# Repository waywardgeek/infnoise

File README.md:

### Infinite Noise TRNG (True Random Number Generator)

For instructions for compiling the and using Infinite Noise TRNG driver, go to the software
sub-directory, and read the [README](software/README.md) file there.  Both Linux and Windows
are supported.

The Infinite Noise TRNG is a USB key hardware true random number generator.  It uses what
I call a "Modular Entropy Multiplier" architecture (previously Infinite Noise Multiplier or
FireBug).  Besides being simple, low-cost, and fast, it is much easier to get right than
other TRNGs.  It naturally defends against influence from outside signals, such as radio
interference and power supply noise, making it simple to build securely, without requiring
an expert in analog design.  Modular entropy multipliers produce a provable and easily
measured level of entropy based on thermal noise, approximately equal to log2(K) per
output bit, where K is a gain between 1 and 2 set by two resistors around an op-amp.  A
"health monitor" can track this and verify that the output entropy is within the expected
range, which for the Infinite Noise TRNG described below is within 2% of log2(1.82).

Modular entropy multipliers are suitable for both board level implementation and ASIC
implementation.  Speed is limited by the speed of a gain stage and a comparator, and can
run in excess of 100 Mbit/second per second with high performance components.  Cheap
solutions with CMOS quad op-amps can run at 8Mbit/second.

Adjacent bits from a modular entropy multiplier are correlated, so whitening is required
before use in cryptography.  This should be done by continually reseeding a
cryptographically secure hash function such as SHA-512, Blake2b, Keccak-1600 (SHA3), or a
stream cipher such as ChaCha.  This implementation uses Keccak-1600 with cryptographically
secure reseeding of more than 400 bits of entropy at a time, overcoming a trickle in/out
problem present in the GNU/Linux /dev/random system.  Users who need many megabytes per second
of data for use in cryptography can set the outputMultiplier as high as they like, which
causes Keccak to generate outputMultiplier\*256 bits per reseeding by the Infinite Noise
TRNG.

The modular entropy multiplier architecture was invented by Peter Allan in 1999, which he
called [Firebug](http://apa.hopto.org/firebug).  I reinvented it in 2013.  As usual, most
of my good ideas are rediscoveries of existing ideas :-)  Peter has his own
version called [the Redoubler](https://github.com/alwynallan/redoubler), which
is awesome.  It really is the _right_ way to generate random bits, whether on a
board with standard parts, or on an custom chip.

### Crowd Supply campaign

With the aid of crowdfunding, the Infinite Noise will soon be produced (again)! The campaign is driven by Manuel Domke, founder of a fresh electronics manufacturing company called 13-37.org electronics. 

[Check the Crowd Supply project page for latest updates](https://www.crowdsupply.com/13-37/infinite-noise-trng)

### The Eagle open-source boards work!

Here is the first completed Infinite Noise USB key.  I offered this model on
Tindie to help get the modular entropy multiplier concept out there initially.

Here are the first three boards from OSH Park.  They work _exactly_ as predicted.  They all
generate 300,000 bits per second, resulting in a measured 259,000 bits of entropy per second, which is within 0.5% of the predicted value of log2(1.82).

All three boards should produce log2(1.82) = 0.864 bits of entropy per bit by design.  The first one is estimated
to produce 0.867, while the second one produces 0.868, and the third is 0.867.

Here is the latest schematic:

![Schematic of Infinite Noise Multiplier](images/infnoise.png?raw=true "Infinite
Noise Multiplier")

Here is the latest board layout (thanks, EagleWorks!):

![Board layout of Infinite Noise Multiplier](images/infnoise_brd.png?raw=true "Infinite
Noise Multiplier")

The breadboard worked, too.  Estimated entropy per bit is 0.81 for the bread-board.  By design, it should
be 0.80, so it is very close to the prediction.  The breadboard proved out much of the theory of operation, as well os providing raw data for entropy testing.

![Breadboard of Infinite Noise Multiplier](images/infnoise_breadboard.jpg?raw=true "Infinite
Noise Multiplier")

Here is the voltage on one of the hold cap:

To build one of these for yourself, you can [order three boards from OSH Park for only
$3.25](https://oshpark.com/profiles/WaywardGeek), and then buy parts from [Digikey and
Mouser as described in the
BOM](https://github.com/waywardgeek/infnoise/blob/master/eagle/BOM.xlsx?raw=true).  I
designed this board to be cheap, not easy to assemble by hand.  I use 2 QFN parts and
three with 0.5mm lead pitch.  If you want to [build these yourself the way I
do](https://www.sparkfun.com/tutorials/59), consider uploading the [infnoise.brd
file](https://raw.githubusercontent.com/waywardgeek/infnoise/master/eagle/infnoise.brd) to
[OSH Stencils](https://www.oshstencils.com/) and ordering a solder paste stencil for $7.
I get the [solder paste from SparkFun](https://www.sparkfun.com/products/12878).  Kudos to
OSH Park, OSH Stencil, SmallBatchAssembly, and DigiSpark!  They're making this whole party
possible!

The total for all the parts, including boards from OSH Park, come to $5.69 each, in 1,000
unit quantities.  However, that cost is dominated by USB related parts, particularly the
FT240X chip, the USB connector, and the USB-stick enclosure.  Just the components for the
modular entropy multiplier come out to $0.97.

Cor van Wandelen was kind enough to create these scatter plots showing the non-randomness
in the raw output.

Here is a faster version that uses a more expensive op-amp from TI:

![Schematic of Infinite Noise Multiplier](infnoise_small/schematic.png?raw=true "Infinite
Noise Multiplier")

### The Problem: Noise Sensitivity, and Signal Injection

True random number generators are very difficult to get right.  Generally, they amplify a
tiny noise signal, perhaps only a microvolt in amplitude, by a factor of millions or
billions, until the signal is an unpredictable digital signal.  This signal is then
sampled to see if it's a 0 or 1.

The problem with this approach is the weak noise source can easily be influenced by other
nearby signals, which may be under the control of an attacker, or perhaps observable by an
attacker, enabling him to predict the output.  Systems built with massive amplification of tiny noise sources often require power supply filters and EMI shielding, and even then remain difficult to prove secure.  Generally, an expert analog designer is needed to get it right.

Intel's RDRAND instruction is a perfect example.  It uses rapid amplification of thermal
noise to determine the power-up state of a latch.  Unfortunately, this source of entropy
is highly power-supply and cross-talk sensitive.  Intel claims to have
carefully shielded their thermal noise source, but without a thorough pubic audit of both
the design and layout, including all potential sources of interference, it is not possible
to trust the RDRAND instruction as the source of entropy for cryptography.

With such strong sensitivity, these TRNG architectures are potential targets for signal
injection by an attacker, who can cause the TRNG to generate his desired output rather
than true random data.

### The Solution: Modular Multiplication

Unpredictable noise sources are tiny, and must be massively amplified to be used by an
TRNG.  Other TRNG architectures amplify these signals until they saturate, becoming
digital 1's and 0's.  They rely on careful design and shielding to keep outside signals
from influencing the noise source.

For example, if we amplify a tiny noise source by 1 billion in a system that saturates at
3.3V, then 1uV of noise will be amplified causing the output to be about 3.3V.  An
attacker need only introduce at least -1uV to cause the TRNG to saturate at 0V instead.
An attacker with even this tiny influence can entirely control the output.

If TRNGs used modular multiplication to amplify their noise source, this noise sensitivity
problem would go away.

If we multiply a 1uV peak by 1 billion modulo 3.3V, then the result will be about 0.3V,
which will result in a digital 0.  If an attacker subtracts 1uV, causing our noise source
to be at 0.0V, then after amplification, the output is 0V, which still results in a 0.  In
fact, without knowing the current amplitude of the noise source, there is no signal an
attacker can add to our noise source to control the output.  He may be able to flip the
output bit, but since it was already random, his signal injection fails to control the
result, which is still random.  In fact, an attacker's injected signal causes the output
to be _more_ random, since an attacker is a nice unpredictable source of entropy!
Infinite Noise Multipliers _add_ entropy from all noise sources, even those from an
attacker.

### Variations

There are currently 3 versions of Infinite Noise Multipliers documented here.  The
infnoise_small directory describes a low part-count design that works well with op-amps
which have rail-to-rail inputs and outputs.  It runs at 4MHz, outputting 0.86 bits worth of
entropy on each clock (loop gain = 1.82), for a total of over 3.4 Mbit of entropy produced
per second.  The infnoise_fast directory contains a 50% faster design that uses a few more
resistors and an additional op-amp.  This design is suitable for use with a wide range of
op-amps.  It runs at 6MHz, outputting 0.86 bits worth of entropy on each clock (loop gain =
1.82), for over 5Mbit of entropy per second.

Because Infinite Noise Mulitpliers are switched-capacitor circuits, it is important to use
components with low leakage, like the OPA4354 CMOS quad op-amp from TI.  Op-amps with
below 1nA of input bias current will enable running at lower frequencies with less power.

To reproduce these simulations, download the TINA spice simulator from Ti.com.

Here is a "small" modular entropy multiplier:

![Schematic of small Infinite Noise Multiplier](infnoise_small/schematic.png?raw=true "Small
Infinite Noise Multiplier")

Note that the upper left op-amp is used as a comparator, and must settle to either 0V or
Vsup before the lower left op-amp can multiply the input by 2X.

Here's a "fast" version that does two multiplications in parallel and uses the comparator
result to select the right one.

![Schematic of fast Infinite Noise Multiplier](infnoise_fast/schematic.png?raw=true "Small
Infinite Noise Multiplier")

There is also a [CMOS version described here](http://waywardgeek.net/RNG).

### Simulations

LTspice was used to simulate the small and fast variations.  Here are simulation waveforms
for the small version:

![Simulation of small Infinite Noise Multiplier](infnoise_small/shortsim.png?raw=true "Small
Infinite Noise Multiplier")
![Simulation of small Infinite Noise Multiplier](infnoise_small/longsim.png?raw=true "Small
Infinite Noise Multiplier")

And again for the fast version.

![Simulation of fast Infinite Noise Multiplier](infnoise_fast/shortsim.png?raw=true "Fast
Infinite Noise Multiplier")
![Simulation of fast Infinite Noise Multiplier](infnoise_fast/longsim.png?raw=true "Fast
Infinite Noise Multiplier")

### Theory of Operation

Consider how a successive-approximation A/D converter works.  Each clock cycle, we compare
the input voltage to the output of a D/A converter, and if it's higher, the next bit out
is 1, and if lower, it's a 0.  We use binary search to zero-in on the analog input value.
Here is a block diagram from Wikipedia:

![Successive approximation A/D block diagram](images/SA_ADC_block_diagram.png?raw=true "SAR
A/D Block Diagram")

There is another way to build a successive-approximation A/D that eliminates the D/A
converter.  Compare the input to Vref (1/2 supply), and if it is larger, subtract Vref
from the input.  Then multiply by 2X.  The bit out is the value of the comparator.

    Vin' = Vin >= Vref? Vin - Vref : Vin

This eliminates the D/A converter, and has no limit on how many bits we shift out.  In
reality, the only reason we do not use this architecture for real A/D converters is that
it's accuracy depends on the accuracy of the multiply by 2X operation.  A simple circuit
with 1% resistors would only achieve about a 7 bit resolution.

However, just because the bits are not accurate does not mean we can't keep shifting them
out.  What are we measuring after shifting 30 times?  It's just noise in the circuit, with
no correlation to the original Vin.  It's totally random unpredictable nonsense.  This is
the idea behind the Infinite Noise Multiplier.

If this A/D converter was perfect, both 0's and 1's should shift out with equal
probability, with no correlation between bits.  This has been verified C simulations and
dieharder.  However, due to accuracy limitations on real components, we cannot multiply by
exactly 2X every cycle.  When the loop amplification is < 2X, the entropy per output bit
is reduced, but can be easily computed.  If E is the entropy per bit, and K is the loop
amplification, then:

    E = log(K)/log(2)

or equivalently:

    E = log2(K)

This provides a simple way to calculate the entropy added to an entropy pool per bit.
The program infnoise.c directly measures the entropy of modular entropy multiplier output,
and compares this to the estimated value.  Both simulations and actual hardware show that
they correlate well.

The "fast" board level version uses two op-amps and comparator to impliment a modular
multiplication using a couple of tricks.  First, multiplication by 2 modulo Vsup is
accomplished by multiplying relative to either GND or Vsup.  When multiplying relative to
GND, a 0.2V signal becomes 0.4V.  When multiplying relative to a 3V Vsup, a 2.8V signal
becomes 2.6V, because 2.8V is 0.2V below 3V, and after 2X, it's 0.4V below 3V.  The math
comes out the same as if I'd multiplied relative to GND, and simply subtracted Vsup if the
result was > Vsup:

    Vsup - 2*(Vsup - Vin) = Vsup - 2*Vsup + 2*Vin = 2*Vin - Vsup
        = 2*Vin mod Vsup

So, we multiply by 2 either way, and only subtract out Vsup if needed.  This is identical
to multiplication modulo Vsup.  The comparator simply selects the output of one of the two
op-amps.  This is the basic analog modular multiplier.

A second trick used to create the "small" version was to notice that the output of the
comparator could be used to combine both multiplier op-amps into 1.  This abuse of the
comparator output needs to be carefully checked.  In particular, the output is generally
treated as a digital signal, but in this case, it is used as an analog singal.  Care
should be taken not to load the OUT signal significantly.

### Provable Entropy, Based on Thermal Noise

The RMS thermal noise generated by a resistor of value R is:

    Vnoise = sqrt(4*Kb*T*deltaF*R)

where Kb is Boltzmann's constant 1.3806504×10-23 J/K, T is temperature in Kelvin (about
293 for room temperature), and deltaF is the frequency range of noise being measured.

For the V1 version of the Infinite Noise boards above, the op-amp has an 8MHz unit gain
crossover, and a low load negative input with 10K Ohms in parallel with 8.2K Ohms, which
is 4.5K Ohms.  Vnoise up to unity crossover is about 24uV, and gets amplified by the
op-amp gain K of 1.82 to about 40uV, and held on a 220pF capacitor.  A 40uV change on the
hold capacitors results in a current of about 55,000 electrons, so the hold capacitors are
able to capture about 15 bits of resolution of this noise signal, which gets amplified by
K and combined with later noise samples in the hold capacitors every cycle.  The
capacitors s hold about 2^31 different charge levels in the range of 0.3V to 3V.  This is
effectively a 31-bit register which we multiply by 1.82 every cycle and add a 15 bit noise
signal.  This results in entropy shifted out just slightly less than log2(1.82), since
this entropy compression does not result in 100% pure entropy (just very close).

changes the output of the comparator several cycles later.  Each cycle, this 15-bit noise
signal is added in, far in excess of the log2(K) of entropy we shift out, enabling us to
concentrate entropy in the hold capacitors, which hold over 2^32 electrons when
discharging from the design range of 3V to 0.3V.  Note that we are not assuming successive
noise samples of this 8MHz noise, when measured at 480KHz, will be completely uncorrelated,
but only that concentrating a 15-bit representation of sequential samples will have a few
bits of "surprise", which is log2(1/probability of guessing the next sample).

### Analysis of Analog Modular Multiplication

Consider a traditional zener TRNG:

    Vzener -> Multiply by 1e9 relative to Vref -> Clamp between -Vsupply and Vsupply -> digital 0/1

For simplicity, assume our amplifier has positive and negative supplies, Vsupply, and
-Vsupply.  If Vzener\*1e9 >= 0, then the output is a digital 1, otherwize 0.

There are variations on this theme, but this is basically how Zener TRNGs work.  The math
computed by this circuit is:

    clamp(-Vsupply, Vsupply, 1e9*Vzener)

where the first two parameters are the lower and upper clamping voltages, and the third
parameter is the amplified signal.

The problem with this design is that an attacker, Malory, can override the tiny zener
noise source with radio-signals, or any of a number of attacks.  Basically, if he can find
a way to add his signal to Vzener, then the circuit does this:

    clamp(-Vsupply, Vsupply, 1e9*(Vzener + Vmallory))

If Vmallory is always just a bit larger than Vzener in magnitude, then Mallory can
completely determine the output, because Mallory can make Vzener + Vmallory greater or
less than zero at will, and after multiplying by 1e9 it the amplifier will saturate in the
direction of the sign of Vmallory.

What if we used modular multiplication instead?  Assume we represent Vzener now as a
positive voltage between 0 and Vsupply so we can use the normal mod operation.  In this
case the normal output would be:

    Vzener*1e9 mod Vsupply -> compare to Vsupply/2 -> 1 if > Vsupply/2, 0 otherwise

This is even _more_ unpredictable than the original version. Only the portion of Vzener
between +/- Vsupply/1e9 made any difference in the output before, but now we use the
entire amplitude of Vzener.  The amplitude of Vzener has additional entropy which now
further whitens the output bit.

When Mallory attacks this system, injecting Vmallory into the same node as Vzener, it
computes:

    (Vzener + Vmallory)*1e9 mod Vsupply = Vzener*1e9 + Vmallory*1e9 mod Vsupply

Let Vz = Vzenner\*1e9 mod Vsupply, and Vm = Vmallory\*1e9 mod Vsupply.  Then the output
is just:

    Vz + Vm mod Vsupply

Vz is unpredictably distributed between 0 and Vsupply, hopefully somewhat uniformly.
How can Mallory determine what to add to it to control the output?  He can not.
His interference can only _increase_ the entropy of the output, since Mallory's attack is
itself an entropy source, further randomizing the result.

### Rolling Up the Loop

A 30-long cascade of switched capacitor 2X modular multipliers is a lot of hardware!
Fortunately, it is possible to reuse the same multiplier for each stage, without even
slowing down the circuit.  In our long chain of 2X modular multipliers, we computed:

    A1(1) = 2*Vzener(0) mod Vsupply
    A2(2) = 2*A1(1) mod Vsupply
    A3(3) = 2*A2(2) mod Vsupply
    ...
    A30(30) = 2*V29(29) mod Vsupply

Here, Vzener(0) is Vzener when sampled at the first clock pulse.  Vzener(n) is the voltage
sampled on the nth clock pulse.  An(i) is the output of the nth 2X modular multiplier at
clock cycle i.  Instead of using 30 stages, what would happen if we simply fed the output
of the 2X modular multiplier stage back on itself?  We'd just have A instead of A1 ..
A30:

    A(1) = 2*Vzener(0) mod Vsupply
    A(2) = 2*(Vzener(1) + A(1) mod Vsupply 
          = 2*Vzener(1) + 4*Vzener(0) mod Vsupply
    A(3) = 2*(Vzener(2) + A(2)) mod Vsupply
          = 2*Vzener(2) + 4*Vzener(1) + 8*Vzener(0) mod Vsupply
    ...
    A(30) = 2*Vzener(29) + 4*Vzener(28) + 8*Vzener(27) + ... + 2^30*Vzener(0) mod
    Vsupply

If 2^30\*Vzener(0) mod Vsupply is an unpredictable value, then the other terms can in no
way reduce this unpredicability.  What if Mallory attacks?  In that case, at step 30, we
have:

    A(30) = 2*(Vzener(29) + Vmallory(29)) + ... + 2^30*(Vzener(0) + Vmallory(0) mod
    Vsupply
            = [2*Vzener(29) + 4*Vzener(28) + ... + 2^30*Vzener(0)] +
              [2*Vmallory(29) + 4Vmallory(28) + ... + 2^30*Vmallory(0)] mod Vsupply

The output is just the signal we had before without Mallory's influence, plus a value
injected by Mallory, mod Vsupply.  Once again if Mallory does not know what the value of
A(30) would have been, he cannot control the result.  He can only make it more random.

The value of A acts as an entropy pool, collecting entropy from all signals that impact
it's value.

### We Don't Need Zener Noise

In reality, there are many sources of unpredictable noise in every circuit.  There's large
predictable and controllable noise, like power supply noise, and tiny 1/f noise in the
multi-gigahertz range.  Shot noise, thermal noise, EMI, cross-talk... you name it, no
matter where we look, there's noise.  Infinite noise multipliers amplify them all in
parallel, and adds them together effectively in an tiny entropy pool.  Zener noise would
be just one more source of noise in a symphony of existing noise sources, and will not
enhance the resulting entropy enough to bother.

A modular entropy multiplier will amplify _every_ source of niose and amplify it until it is
larger than Vsupply.  It adds them together and amplifies them in parallel.  Every device
in the signal path loop contributes. 

With N sources of noise, the output looks like:

    V1(1) = Vnoise1(1) + Vnoise2(1) + Vnoise3(1) ... VoinseN(1)
    ...
    V1(30) = [2*Vnoise1(29) + 4*Vnoise1(28) + ... + 2^30*Vnoise1(0)] +
             [2*Vnoise2(29) + 4*Vnoise2(28) + ... + 2^30*Vnoise2(0)] +
             ...
             [2*VnoiseN(29) + 4VnoiseN(28) + ... + 2^30*VnoiseN(0)] mod Vsupply

Each individual noise sources contributes its own power-of-two sequence to the total.
A micro-volt noise source contributes nearly as strongly as a Vsupply/10 amplitude noise
source.

The mashing together of noise source data with unbounded modular multiplications leads to
awesome entropy levels.  Just how awesome?  Consider just thermal noise from one resistive
summing node (the minus terminal on op-amp in the 2X gain stage).

How correlated are successive samples?  How badly does this impact our output?  It turns
out that high correlation is OK.  What we want is high resolution contribution of noise
samples, even more than low correlation.

Suppose sample Vnoise(0) is 1.034 uV, and Vnoise(1) is 1.019 uV.  That is
some bad correlation, but 14 clock cycles later, the difference in amplitudes between
these samples will have the output toggling unpredictably.  What matters is not
correlation between noise samples, but the accuracy to which we can remember the
difference between them in our circuit.  This should be limited only by electron counts on
our hold capacitor.  It has an integer number of electrons at any time.  About 2.5 billion
electrons flow out of 100pF holding caps when charging from 0.5V to 4.5V.  That's about 31
bits of resolution.  Every time we capture noise on these caps, it adds or subtracts an
integer number of electrons.  Each electron contributes about 1.6nV on our hold cap.  So
long as we can capture noise that has significantly more than 1.6nV of unpredictability,
we should be able to keep the output generating close to 1 bit of entropy per clock.  In
this example, both noise samples had over 10X the minimum resolution in unpredictable
noise, and easily contributed a bit of entropy each to our 31-ish bit entropy pool.

### Whitening the Right Way

Data coming from true random number generators is never 100% random.  I am aware of no
exceptions.  Whitening is required in all cases before the data is suitable for use in
cryptography.

Most TRNGs build whitening into the hardware.  This is a _mistake_, at least if the
whitening cannot be turned off.  Respectable TRNGs, such as [OneRNG](http://onerng.info/)
and [Entropy Key](http://www.entropykey.co.uk/) provide hardware whitening, but also
provide access to the raw data streams for health analysis.

I prefer to follow the KISS rule when it comes to security.  The more complex the TRNG
key, the more likely it is insecure.  Therefore, the initial Infinite Noise Multiplier
does not even have a microcontroller onboard, and only returns raw data, direct from the
noise source.  Whitening is done in the Infinite Noise driver.

The Infinite Noise driver uses the reference version of the SHA3 "sponge", called Keccak,
with a 1600 bit state.  To make the state of the sponge unpredictable, it is initialized
with 20,000 bits of of Infinite Noise data before any data is output.  After that, reading
bytes from the SHA3 sponge blocks until twice as many bytes of entropy have been fed into
the sponge from the Infinite Noise TRNG.

### Non-Power-of-Two Multiplication

The circuit shown in infnoise_fast multiplies by 1.82 every clock rather than 2.0.  As
stated above, this reduces the entropy per output bit to log(1.82)/log(2) = 0.86 bits of
entropy per output bit.

Suppose in cycle 0, the noise Vnoise(0) is +/- Vsupply/2^30V every cycle.  At most 31 clock
cycles can go by before the output toggles due to Vnoise(0), because on cycle 31, it's
contribution will be 2\*Vsupply, and the remaining noise contributions can do no more than
subtract Vsupply.  This will have to be subtracted out.  The cycle x1 where we know
Vnoise(0) will have toggled the output is:

    Vnoise(0)*2^x1 >= 2*Vsupply
    2^x1 >= 2*Vsupply/Vnoise(0)
    x1 >= log(2*Vsupply/Vnoise(0))/log(2)

When multiplying by K, where 1 < K < 2, it takes more clock cycles for Vnoise(0) to reach
Vsupply, insuring that it will have changed the output.  The cycle x2 when this happens
is:

    Vnoise(0)*K^x2 >= 2*Vsupply
    K^x2 >= 2*Vsupply/Vnoise(0)
    x2 >= log(2*Vsupply/Vnoise(0))/log(K)

The ratio of the clocks it takes with amplification 2 vs K is:

    x1/x2 = [log(Vsupply/Vnoise(0))/log(2)] / [log(Vsupply/Vnoise(0))/log(K)]
          = log(K)/log(2)

It takes log(2)/log(K) more cycles to insure the output is different.
the entropy shifted out with exactly 2X amplification will be 1 bit per clock.

### Health Monitoring

Infinite Noise Multipliers output entropy at a predictable rate, which is measured
continually.  If the entropy per bit deviates from the theoretical value of log(K)/log(2)
by more than 2% during the previous 80,000 bits, then the driver stops generating output.
Some deviation is expected, since K is dependent on two resistor values, which can be off
by 1% each.  Also, a significant amplitude noise in the system, as well as "misfires", can
cause more entropy to be output than predicted.  The estimated entropy per bit are
continually estimated and compared to expected values.

Entropy per bit is measured as the log2 of one over the probability of seeing a specific
output sequence from the modular entropy multiplier.  The probability of any given output
bit is estimated by keeping a history of results, given the previous 7 bits.  Simulations
with K=1.82 show that using 16 bits rather than 7 gives only a 0.16% improvement in
prediction accuracy, so only 7 are used.

### Entropy Testing

A common program used to estimate entropy in a data stream is "ent".  A sample data file
was created this way (using one of the original V1 boards):

    $ sudo ./infnoise-v1 --raw --debug > foo
    ...
    Generated 14680064 bits.  OK to use data.  Estimated entropy per bit: 0.866710, estimated
    K: 1.823500
    num1s:49.888504%, even misfires:0.159748%, odd misfires:0.127300%
    Generated 15728640 bits.  OK to use data.  Estimated entropy per bit: 0.866856, estimated
    K: 1.823684
    num1s:49.901504%, even misfires:0.145973%, odd misfires:0.160365%
    Generated 16777216 bits.  OK to use data.  Estimated entropy per bit: 0.867010, estimated
    K: 1.823879
    num1s:49.963040%, even misfires:0.146815%, odd misfires:0.145067%

Here's ent's results on the raw data stream this run produced:

    $ ent foo
    Entropy = 7.318058 bits per byte.
    
    Optimum compression would reduce the size
    of this 2072576 byte file by 8 percent.
    
    Chi square distribution for 2072576 samples is 1510131.51, and randomly
    would exceed this value 0.01 percent of the times.
    
    Arithmetic mean value of data bytes is 127.5088 (127.5 = random).
    Monte Carlo value for Pi is 3.427100794 (error 9.09 percent).
    Serial correlation coefficient is -0.005035 (totally uncorrelated = 0.0).

The health monitor does a much better job at estimating the entropy than ent.  The actual
non-randomness is 60% higher than ent predicted.  Ent said 0.915 bits of entropy per bit,
while the health monitor measured 0.867.  The health monitor's entropy estimator is just a
tiny fraction of a percent higher than the model predicts, while ent is off by 4.8% .  The
design target for entropy per bit was log2(1.82) = log(1.82)/log(2) = 0.864.  This is set
by two resistors.  Based on entropy measured by the health monitor, it could compress this
file by 13.3%.

The entropy estimator is based on the model that:

- The device is not rapidly changing the sort of numbers it puts out, so history can be
  used as a guide.
- There is no special state stored in the modular entropy multiplier that could cause data
  to be different each clock cycle, other than on even/odd cycles.
- Bits further away are less correlated.

The first assumption is strong assuming an attacker is not involved.  An attacker
injecting a strong signal could mount a DoS attack, since the health monitor would detect
entropy being too high, and would disable output.  This is a conscious choice: the health
monitor could instead simply warn that entropy seems too high.  Turning off the output
when an attacker may be present seems the safer choice.

The second assumption relies on the fact that only two nodes store state in this
implementation of a modular entropy multiplier, and that the outputs are sampled from
even/odd comparator outputs on even/odd cycles.  Other TRNGs may not satisfy this
assumption if they have additional internal state.  However, a typical zener TRNG should
satisfy this assumption.

The third assumption really does require a modular entropy multiplier.  A zener TRNG would
most likely have strong 60 Hz correlations from 60 Hz noise, for example.  This is also
true of A/D converter based TRNGs.  With a modular entropy multipliers, these signal sources
are added to a signal already saturated with thermal noise, making it in no less random.
Every cycle, a new thermal noise sample is added to the state, causing less correlation
with previous states.

### Future Version

I'm really just having fun with this project.  I personally prefer this version

I plan on only making this version going forward, even though I doubt it will sell very
well.  That's OK, because I don't make any money on them :-)

### Credits

Peter Allan has been very helpful in moving this project forward.  The github user known
as EagleWorks did an _amazing_ job redoing the board layout.  Somehow, my ameraturish work
just wasn't good enough for him :-)  Thanks, EagleWorks!  Cor van Wandelen created the
color and scatter plots.

### Free As in Freedom

The modular entropy multiplier architecture was invented in 1999 by Peter Allan, but was not
patented at that time.  Peter is working with me to make modular entropy multiplier/Firebug
open-source hardware, unencumbered by patents or copyright.

I reinvented with the modular entropy multiplier architecture in 2013, and the board level
versions in 2014.  I hereby renounce any claim to copyright and patent rights related to
any changes or improvements I may have made to this architecture.  Furthermore, I am aware
of no infringing patents and believe there are none.  It should be entirely safe for use
in any application.  Feel free to copy anything here, and even sell your own modular
noise multiplier based USB keys based on this work.

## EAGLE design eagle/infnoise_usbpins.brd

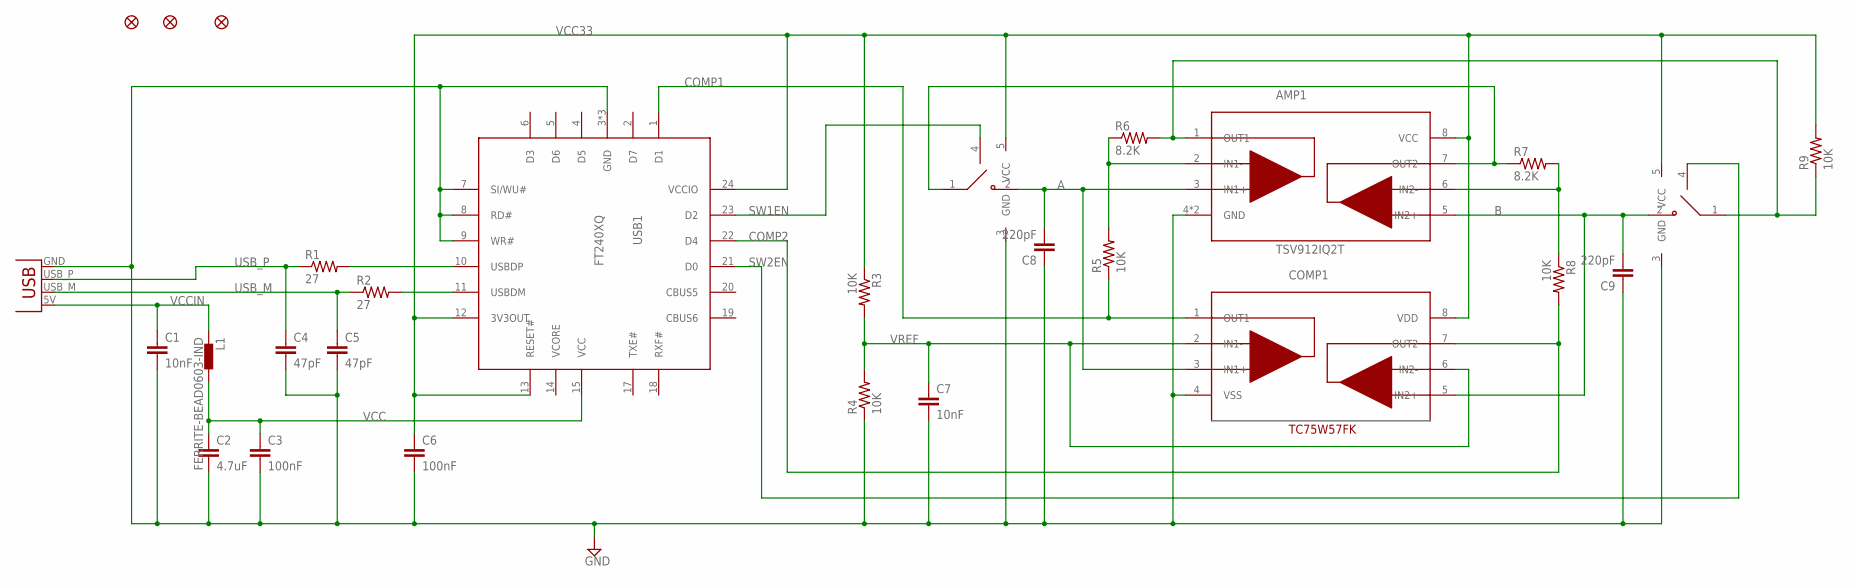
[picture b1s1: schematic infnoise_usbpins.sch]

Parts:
AMP1: TSV912IQ2T; DFN8-2X3
C1, C7: 10nF; 0603-CAP
C2: 4.7uF; 0603-CAP
C3, C6: 100nF; 0603-CAP
C4, C5: 47pF; 0603-CAP
C8, C9: 220pF; 0603-CAP
COMP1: TC75W57FK; SSOP8-P-0.50A
FID1, FID2, FID3: FIDUCIALUFIDUCIAL; MICRO-FIDUCIAL
L1: FERRITE-BEAD0603-IND; 0603-IND
R1, R2: 27; 0603-RES
R3, R4, R5, R8, R9: 10K; 0603-RES
R6, R7: 8.2K; 0603-RES
SW1, SW2: MC74VHC1G66DFT1G; SC70-5L
USB1: FT240XQ; QFN24-4X4
X1: USBRAWPINS; USB-A-RAWPINS

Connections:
A: AMP1.3 (IN1+), C8.2, COMP1.3 (IN1+), SW1.2 (NO)
AMP1OUT: AMP1.1 (OUT1), R6.2, R9.1, SW2.1 (COM)
AMP2OUT: AMP1.7 (OUT2), R7.1, SW1.1 (COM)
B: AMP1.5 (IN2+), C9.2, COMP1.5 (IN2+), SW2.2 (NO)
COMP1: COMP1.1 (OUT1), R5.1, USB1.1 (D1)
COMP2: COMP1.7 (OUT2), R8.2, USB1.22 (D4)
FB1: AMP1.2 (IN1-), R5.2, R6.1
FB2: AMP1.6 (IN2-), R7.2, R8.1
GND: AMP1.4 (GND), AMP1.EXP (GND), C1.2, C2.2, C3.2, C4.2, C5.2, C6.2, C7.2, C8.1, C9.1, COMP1.4 (VSS), R4.1, SW1.3 (GND), SW2.3 (GND), USB1.3 (GND), USB1.7 (SI/WU#), USB1.8 (RD#), USB1.9 (WR#), USB1.16 (GND), USB1.EXP (GND), X1.GND
unnamed: R1.2, USB1.10 (USBDP)
SW1EN: SW1.4 (IN), USB1.23 (D2)
SW2EN: SW2.4 (IN), USB1.21 (D0)
USBDM: R2.2, USB1.11 (USBDM)
USB_M: C5.1, R2.1, X1.USB_M (D-)
USB_P: C4.1, R1.1, X1.USB_P (D+)
VCC: C2.1, C3.1, L1.2, USB1.15 (VCC)
VCC33: AMP1.8 (VCC), C6.1, COMP1.8 (VDD), R3.1, R9.2, SW1.5 (VCC), SW2.5 (VCC), USB1.12 (3V3OUT), USB1.13 (RESET#), USB1.24 (VCCIO)
VCCIN: C1.1, L1.1, X1.5V (VCC)
VREF: C7.1, COMP1.2 (IN1-), COMP1.6 (IN2-), R3.2, R4.2

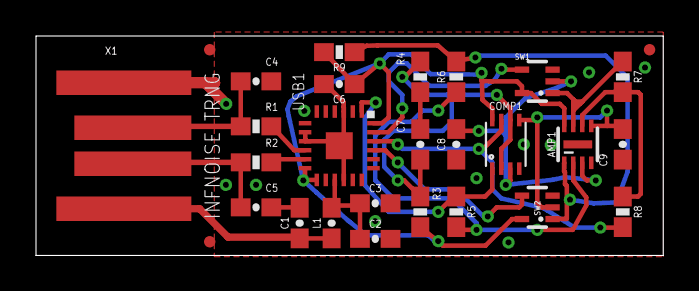
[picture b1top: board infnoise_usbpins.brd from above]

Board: 2 copper layers, 34.8 x 12.2 mm, 28 parts (0 on the bottom side), 19 nets.

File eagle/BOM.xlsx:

Inf Noise Parts | Price | Buy size | Num used |  | Over-buy | Reel charge | Total Cost |  | Price | Buy size |  | Refs | Value | User supplied | Supplier | Sup. P/N | Man. P/N | Package | Notes
SPST switch | 0.07774 | 1000 | 2 | 0.15548 | 0.2 | 7 | 162.48 |  | 0.2364 | 25 | 0.4728 | SW1,SW2 |  | 1 | Digikey | MC74VHC1G66DFT1GOSCT-ND | MC74VHC1G66DFT1G | SC-70
Dual op-amp | 0.3795 | 1000 | 1 | 0.3795 | 0.2 | 7 | 386.5 |  | 0.847 | 10 | 0.847 | AMP |  | 1 | Digikey | 497-12414-1-ND | TSV912IQ2T | DFN8 (2x2mm)
Dual comparator | 0.2904 | 1000 | 1 | 0.2904 | 0.2 | 7 | 297.4 |  | 0.57 | 10 | 0.57 | CMP |  | 1 | Digikey | TC75W57FKTE85LFCT-ND | TC75W57FK | SSOP8-P-0.50A
220pF chip cap | 0.0102 | 1000 | 2 | 0.0204 | 0.2 | 7 | 27.4 |  | 0.0226 | 50 | 0.0452 | C8,C9 | 220pF | 1 | Digikey | 490-1435-1-ND | GRM1885C1H221JA01D | 0603-CAP
8.2K 1% resistors | 0.01711 | 1000 | 2 | 0.03422 | 0.2 | 7 | 41.22 |  | 0.0436 | 50 | 0.0872 | R6,R7 | 8.2K | 1 | Digikey | 541-8.20KHCT-ND | CRCW06038K20FKEA | 0603-RES
10K 1% resistors | 0.01711 | 1000 | 5 | 0.08555 | 0.2 | 7 | 92.55 |  | 0.0436 | 50 | 0.218 | R3,R4,R5,R8,R9 | 10K | 0 | Digikey | 541-10.0KHCT-ND | CRCW060310K0FKEA | 0603-RES
10nF chip cap (see alternate) | 0.00465 | 1000 | 2 | 0.0093 | 0.2 | 7 | 16.3 |  | 0.01 | 50 | 0.02 | C1,C7 | 10nF | 0 | Digikey | GCM188R71E103KA37D-ND | GCM188R71E103KA37D | 0603-CAP | Alternate: GRM188R71H103KA01J/490-7213-1-ND
Total for Inf Noise Mult |  |  | 15 | 0.97485 |  |  | 1023.85 |  |  |  | 2.2602 |  |  |  |  |  |  |  | Note: C1 is included up here, but is actually part of the USB interface
USB Related Parts
USB interface IC | 1.6226 | 1000 | 1 | 1.6226 | 0.2 | 7 | 1629.6 |  | 2.44 | 10 | 2.44 | U1 |  | 1 | Digikey | 768-1157-ND | FT240XQ
.1uF bypass cap | 0.0048 | 10000 | 2 | 0.0048 | 0.2 | 7 | 55 |  | 0.0104 | 50 | 0.0104 | C3,C6 | 0.1uF | 0 | Digikey | 490-1524-1-ND | GRM188R71E104KA01D | 0603-CAP
Ferrite bead | 0.01137 | 1000 | 1 | 0.01137 | 0.2 | 7 | 18.37 |  | 0.03 | 10 | 0.03 | L1 |  | 1 | Digikey | 1276-6355-1-ND | CIC10J601NC | 0603-IND
4.7uf bypass cap | 0.0297 | 1000 | 1 | 0.0297 | 0.2 | 7 | 36.7 |  | 0.0634 | 50 | 0.0634 | C2 | 4.7uF | 1 | Digikey | 490-3302-1-ND | GRM188F51A475ZE20D | 0603-CAP
47pF chip cap | 0.0072 | 10000 | 2 | 0.0144 | 0.2 | 7 | 79 |  | 0.0156 | 50 | 0.0312 | C4,C5 | 47pF | 1 | Digikey | 490-1419-1-ND | GRM1885C1H470JA01D | 0603-CAP
27 Ohm resistor | 0.01711 | 1000 | 2 | 0.03422 | 0.2 | 7 | 41.22 |  | 0.0436 | 50 | 0.0872 | R1,R2 | 27 Ohms | 1 | Digikey | 541-27.0HCT-ND | CRCW060327R0FKEA | 0603-RES
USB SMT male conn | 0.705 | 1000 | 1 | 0.705 | 0.05 | 7 | 712 |  | 1.09 | 10 | 1.09 | X1 |  | 1 | Digikey | WM3983CT-ND | 480372200 | USB-A-SMT-MALE | From Molex
Enclosure | 1.45 | 1000 | 1 | 1.45 | 0.05 |  | 1450 |  | 1.8 | 10 | 1.8 |  |  |  | Mouser | 789-P3A-140703-U | P-140703 |  | From New Age Enclosures: Buy with USB-A opening!
Boards from OshPark | 0.845555555555555 | 900 | 1 | 0.845555555555555 | 0.111111111111111 |  | 761 |  | 1.17 | 12 | 1.17
 |  |  | 10 | 4.71764555555556 |  |  | 4782.89 |  |  |  | 6.7222
EMI shielding | 1 | 1000 | 1 | 1 |  |  | 0 |  |  |  |  |  |  |  |  |  |  |  | Application of silver EMI shielding paint
Assembly | 1.84 | 1000 | 1 | 1.84 |  |  | 1490.4 |  | 10 boards 15x6 = 9 to assemble + 1 spare |  |  |  |  |  |  |  |  |  | http://www.smallbatchassembly.com - will have to modify design
Test | 1 | 1000 | 1 | 1 |  |  | 0 |  | Num boards: | 810
1st class mail | 0.98 | 1 | 1 | 0.98 |  |  | 793.8
Bubble envelope | 0.17 | 500 | 1 | 0.17 |  |  | 170 |  |  |  |  |  |  | uline | S-8059
 |  |  |  | 4.99 |  |  | 2454.2
Subtotal |  |  |  | 10.6824955555556 |  | Total cash | 8260.94
Margin |  |  |  | 1.34 |  | Price/board | 10.1986913580247 |  | Note: margin includes EMI shielding and test charge, plus handling fee
 |  |  |  |  |  | After margin | 13.6662464197531
Tindie charges |  |  |  |  |  |  | 1.32496848148148 |  | Tilndie charges only 5% + payment processing fee of 2.1-2.9% + $0.30
Total |  |  |  |  |  |  | 14.9912149012346

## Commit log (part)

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2014-10-26 Check each group of 512 bits for having enough entropy
2014-10-28 Tightened the bounds on acceptable entropy generation to be no more than 2% over or under predected entropy
2014-11-02 typo
2014-11-02 Switched to a USB connector designed for 1.6mm thick boards
2014-11-03 Updated BOM
2014-11-07 Library tweaks (non-structural)
    I've adjusted the library as follows:
    Changed text alignment (centered, mostly) on parts, made positioning
    more consistent.
    Reduced tKeepout as it was a rather on the generous side for the 0402
    and 0403 parts.
    Added / fixed a few Device descriptions.
2014-11-08 Board layout changed
    I moved the components on the board around to give a better visual
    representation of the components of the infnoise; USB protection,
    filter, divider network, and then where the actual magic happens. Vias
    galore, but ERC and DRC satisfied.
2014-11-08 Added initial mostly complete dieharder log
2014-11-12 Checking timing failures on bit-bang vs loading
2014-11-13 Added credits
2014-11-14 renamed BOM-81 to BOM-80
2014-11-14 Added pannel with fudicials, courtesy of OSH Park
2014-11-17 Working on edge-connector hack version
2014-11-22 Updated BOM for USPS business mailing pricing
2014-11-23 Cleaned up edge connector board a bit
2014-11-26 Made 0.5mm pads all the same size and shrank QFN24 center pad
2014-12-05 Got it working on Raspberry Pi
2014-12-05 Added entcheck
2014-12-05 Added hashlet data
2014-12-07 Added initial Windows driver
2014-12-10 Added bin2hex
2014-12-21 Minor updates
2015-01-08 Updating README
2015-01-23 changes to includes paths
    made changes to the includes in the infnoise_win.c so that the project
    will build out of the box on windows
2015-01-29 Added photo
2015-03-07 Changed gain target to 1.84
2015-03-10 Clear some compiler warnings.
2015-03-10 This feels like a slightly cleaner way to compile on Fedora without messing with other distributions.
2015-05-18 Removed old _v1_ executable - it is still available in git for anyone who needs it
2015-07-08 Modified behaviour of output multiplier so that 0 means ouitput all the entropy we generate
2015-08-18 Applied daemon patch, thanks to Rune Magnussen
2015-08-23 win: 0D error, pathnames, broken build, warnings
2015-08-24 Removed infnoise_win.h
2015-08-24 Added -I /usr/include/libftdi1 to compile on some Linux platforms
2016-01-28 Switched order of bits in byte in entcheck
2016-02-08 Added udev documentation, thanks to github user Abigail
2016-06-17 add a .service file for use with systemd, assumes the hwrng is plugged in!
2016-06-29 Minor Makefile edit
2016-09-07 Fix typo in README.md
2017-03-26 Initialize Keccak before use
2017-07-25 Added udev rule to start the TRNG via systemd
2017-07-26 Add udev symlink to stop service...
    .. when device is unplugged.
2017-07-27 Update Makefile
    Make without parameters tries to install - corrected by moving install section to the bottom of Makefile.
2017-07-28 Added install & postinstall targets
2017-07-28 Added install for $(PREFIX)/sbin
2017-08-29 Implemented --serial and --list-devices to specify device to start for
2017-08-29 renamed constants
2017-08-29 finally renamed constants...
2017-08-30 software/README: add note on init_scripts folder
2017-08-30 move archlinux systemd file into init_scripts folder
2017-08-30 updated readme
    added repos and link to releases
    updated udev rule
    new command line options --serial and --list-devices
2017-09-10 Fix compiler-warning from GCC 6.4
    Redefining #defines gives a warning. That is trated like an error
    with current compiler options.
2017-09-15 Add OpenRC based init script for Gentoo
    Add a startup script for OpenRC based Gentoo-systems-
2017-12-01 Only force new entropy once a minute when backgrounded
    Make the poll-timeout one minute if the option --daemon is used.
    This saves a lot og CPU-time.
2017-12-23 improved error handling for listing devices and nicer output
2017-12-23 formatting
2017-12-31 make systemd service configurable via /etc/infnoise.conf
2017-12-31 code cleanup
2018-01-04 Always se long poll() timeout
    Many init systems do their own backgrounding so use long timeout
    unconditionally. Change suggested by Manuel Domke.
2018-01-29 update BOM with Mouser part numbers, as DigiKey no longer carries the TC75W57FK and some of the passives are also either gone or on their way out
2018-02-07 Correct CS spelling
2018-02-22 added test results
2018-02-22 moved plots and samples to "tests"
2018-02-22 update references after moving plots to tests/
2018-02-26 --help returns with exit-code 0 now. rc=1 when errors in option parsing.
2018-02-26 fixed plot creation
2018-03-01 finished assigning models to PCB
2018-03-01 also -v
2018-03-01 no debbuild
2018-03-01 still struggling with archlinux version numbers
2018-03-01 fixed release attributes of rpms and archlinux
2018-03-02 initialize opts.version to false
2018-04-02 fix build
2018-04-02 fix infnoise-tools centos
2018-04-02 fix rpm
2018-04-02 add udev rule to make it accessible for non-root users
2018-04-09 more key safety
2018-04-15 first shot for a libinfnoise approach
2018-04-18 clean up libinfnoise.h
2018-04-19 build shared library
2018-04-21 fix locations in makefile (#52) and use libftdi-config (#53)
2018-04-21 bats tests for the driver + libinfnoise cleanup
2018-04-22 add libinfnoise usage examples
2018-04-22 fix infnoise-tools build & libinfnoise
2018-04-22 update Makesfiles (for #53 and #56)
2018-05-02 switch to 13-37-org fork for building packages
2018-05-06 fix Makefile for centos build
2018-06-25 Fix apt-key add command in README
    The apt-key add command was inconsistent with the filename used in the wget command.
2018-06-28 Just removed a whitespace
2018-06-28 Fix for the PKGBUILD
2018-06-28 Further missing include
2018-06-28 Fix related to missing include (PATH_MAX)
2018-06-28 Reverted to the old format to retrieve the version
2018-07-06 -DLINUX in Makefile.linux
2018-07-07 Use getopt_long() for parsing command options
2018-07-09 renaming readme so git formats the markdown
2018-07-13 adapt renaming the Makefiles
2018-07-17 refactored outputBytes (/dev/random not working yet)
2018-07-17 set entropy to 0
2018-07-24 finish infnoise_context & start work on listUSBDevices (to return a device list struct)
2018-07-26 fix --list-devices (still buggy, but works!)
2018-08-11 remove libinfnoise dependancy from binary
2018-08-11 remove debug messages
2018-08-15 fix --dev-random mode (multipliers still buggy)
2018-09-03 Added Makefile.darwin
2018-09-03 fix formatting of usage output
2018-09-05 initialize infnoise_context properly
2018-09-05 fix result size for output buffer
2018-09-07 optimize buffer size when multiplier <= 2
2018-10-01 update archlinux pkgbuild - thanks to @AidanGG
2018-10-03 update shebang for build helperscripts
2018-10-03 fix path to build-files
2018-10-03 moved test results & update README
2018-10-04 fix archlinux build (and removed i686 support)
2018-10-04 update libinfnoise examples
2018-10-12 fix file permissions
2018-10-15 sign sources
2018-10-29 try to fix rpm build (+debug)
2018-10-31 Add manpages for all commands
2019-01-04 Fix macOS install instructions
2019-01-13 fix #15: return actual bytes written from readData()
2019-03-20 Improve code quality
2019-03-21 In case fprintf() fails, still close the file descr.
2019-03-21 Improved readability of daemon.c
2019-03-21 version should be printed, before any env is read
2019-03-21 Reference variable instead of writing type again
2019-03-21 Fix indent
2019-03-24 reduce amount of if-checks in healthcheck
2019-03-24 Specify lenght of output array explicitly
2019-03-24 Unrequired i counting
2019-03-27 Feature: clean shutdown
2019-03-27 Wait until /dev/random is truly required
2019-03-28 ftdi_usb_find_all() requires a free()
2019-03-31 Fix when no device available
2019-03-31 Remote unrequired struct
2019-04-01 Work on bytes instead of bits
2019-04-16 inmWriteEntropyEnd only works on Linux
2019-06-22 Merge the FTDI construction
    Since there's already a conditional in the shell invocation, it might
    as well be used to determine the value of FTDI directly.
2019-07-07 Updated to build in Windows properly, with binary pipe capability
    These changes should NOT affect other (non-Windows) targets
    I used https://github.com/jj1bdx/infnoise-windows as a reference point
    for getting this working (and for the idea to not directly include
    FTDI source files here but instead direct the user to install them).
2020-04-15 Removed unrequired header definitions
2020-04-15 BytesGiven is part of keccak only
2020-04-15 Remove unrequired bytesWritten
2022-01-27 Include poll.h instead of sys/poll.h
    `poll.h` is the POSIX standard include location, and MUSL
    libc issues a warning (which infnoise's `-Werror` in CFLAGS
    makes into an error).
    For more context:
    - [Linux manpage for `poll(2)`][1]
    - [Open Group UNIX Specification][2]
2023-02-11 fixed compiler warning:
    findlongest.c:101:28: error: argument 1 value ‘2147483648’ exceeds maximum object size 2147483647 [-Werror=alloc-size-larger-than=]
    101 | uint8_t *stringsSeen = calloc((uint64_t)1 << (MAX_STRING_SIZE-3u), sizeof(uint8_t));
    | ^~~~~~~~~~~~~~~~~~~~~~~~~~~~~~~~~~~~~~~~~~~~~~~~~~~~~~~~~~~~
2023-06-08 change exit() calls to return false for health checks
2026-03-13 add kernel module for infnoise (experimental)
2026-04-11 fix Makefile.darwin: hardcoded libftdi path, wrong install dir, bogus systemd targets
    - Replace hardcoded /usr/local/Cellar/libftdi/1.4/ with dynamic
    $(shell brew --prefix libftdi) resolution, matching Makefile.macos
    - Fix install target: $(PREFIX)/bin -> $(PREFIX)/sbin to match
    Makefile.linux and Makefile.macos (service files expect /usr/local/sbin)
    - Remove udev rules, systemd service install, and postinstall targets
    that referenced systemctl — these are Linux-only and do not belong
2026-04-11 kmod: add DKMS support for persistent module installation
    Add dkms.conf and Makefile targets (dkms-install, dkms-uninstall) so the
    module persists across kernel upgrades without manual rebuilds.
    Usage:
    make dkms-install # add, build, install via DKMS
    make dkms-uninstall # remove DKMS module and source
    Tested: dkms add/build/install/remove cycle on Arch Linux,
2026-04-12 kmod: add userspace test harness and Makefile test target
    make test runs all tests (~45s):
    - 8 kmod tests (test_infnoise.c): chardev read, hwrng read,
    O_NONBLOCK, GET_STATS, GET_ENTROPY, SET_RAW, bad ioctl,
    open/close/reopen
    - FIPS 140-2 via rngtest (skips if not installed)
    - Shannon entropy via ent (skips if not installed)
2026-04-12 kmod: zero stats struct to avoid kernel stack infoleak in GET_STATS
    infnoise_ioctl() declared `struct infnoise_stats stats` on the stack and
    passed it to infnoise_health_get_stats(), which fills the nine named
    fields but does not touch the six bytes of trailing padding required by
    the struct's u64 alignment. The full sizeof(stats) == 40 bytes was then
    copied to userspace via copy_to_user(), leaking six bytes of
    uninitialized kernel stack contents on every INFNOISE_GET_STATS call.
2026-04-12 kmod: add compat_ioctl for 32-bit userspace on 64-bit kernels
    struct infnoise_stats contains a u64 followed by u32s and u8s. On
    64-bit kernels, u64 has 8-byte alignment and the struct is padded to
    40 bytes. On 32-bit, u64 has 4-byte alignment and padding yields 36
    bytes. The _IOR macro encodes sizeof() into the ioctl number, so a
    32-bit process gets a different ioctl number and copy_to_user copies
    the wrong size — returning garbage or triggering -ENOTTY.
2026-04-21 eliminate global state: move all globals into infnoise_context
    Move 25 file-scope globals (2 in libinfnoise.c, 23 in healthcheck.c) into
    the per-device infnoise_context struct, enabling thread-safe multi-instance
    use of the library.
    New struct infnoise_health_state embedded in infnoise_context holds all
    health checker state (prediction tables, entropy counters, sequential bit
    trackers). Keccak sponge state and USB clock buffer also moved into context.

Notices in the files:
parts and their libraries:
SparkFun-Aesthetics: Licensing: Creative Commons ShareAlike 4.0 International - https://creativecommons.org/licenses/by-sa/4.0
